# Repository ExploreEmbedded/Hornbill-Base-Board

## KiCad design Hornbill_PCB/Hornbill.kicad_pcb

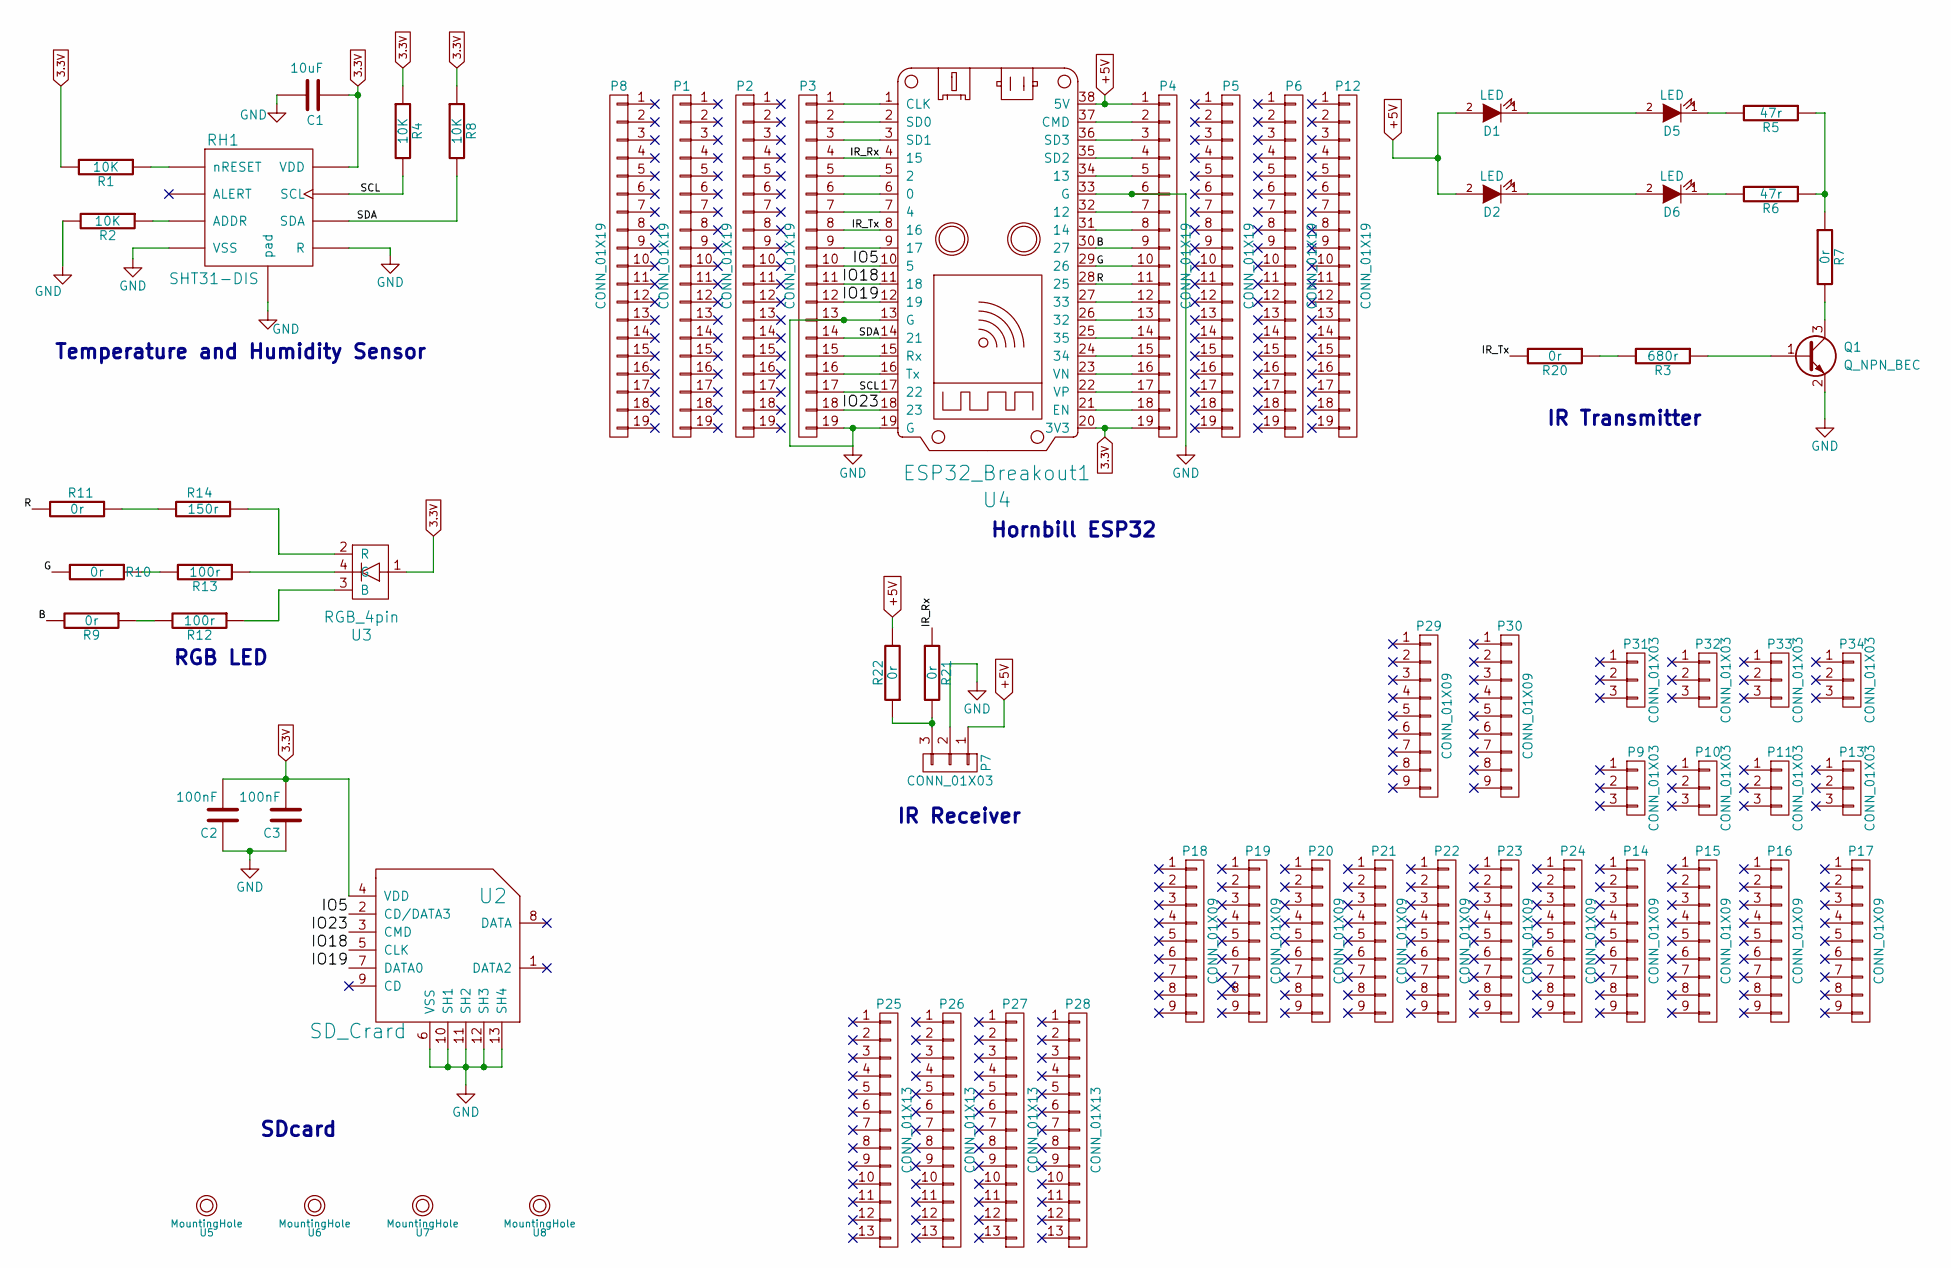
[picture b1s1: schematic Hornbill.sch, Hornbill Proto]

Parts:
C1: 10uF; C_0603_HandSoldering
C2, C3: 100nF; C_0603_HandSoldering
D1, D2, D5, D6: LED; LED-3MM
P1, P2, P3, P4, P5, P6, P8, P12: CONN_01X19; Pin_Header_Straight_1x19_Pitch2.54mm
P7, P9, P10, P11, P13, P31, P32, P33, P34: CONN_01X03; Pin_Header_Straight_1x03_Pitch2.54mm
P14, P15, P16, P17, P18, P19, P20, P21, P22, P23, P24, P29, P30: CONN_01X09; Pin_Header_Straight_1x09_Pitch2.54mm
P25, P26, P27, P28: CONN_01X13; Pin_Header_Straight_1x13_Pitch2.54mm
Q1: Q_NPN_BEC; SOT_23
R1, R2, R4, R8: 10K; R_0603_HandSoldering
R3: 680r; R_0603_HandSoldering
R5, R6: 47r; R_0603_HandSoldering
R7, R9, R10, R11, R20, R21, R22: 0r; R_0603_HandSoldering
R12, R13: 100r; R_0603_HandSoldering
R14: 150r; R_0603_HandSoldering
RH1: SHT31-DIS; DFN-8_SHT-3x-DIS
U2: SD_Crard; Micro_SD
U3: RGB_4pin; RGB_SMD_4pin_New
U4: ESP32_Breakout1; ESP32_Breakout
U5, U6, U7, U8: MountingHole; Mounting

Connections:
3.3V: C1.1, C2.2, C3.2, P4.19, R1.2, R4.1, R8.1, RH1.5 (VDD), U2.4 (VDD), U3.1, U4.20 (3V3)
+5V: D1.2 (A), D2.2 (A), P4.1, P7.1, R22.2, U4.38 (5V)
/B: P4.9, R9.2, U4.30 (27)
/G: P4.10, R10.2, U4.29 (26)
/IO5: P3.10, U2.2 (CD/DATA3), U4.10 (5)
/IO18: P3.11, U2.5 (CLK), U4.11 (18)
/IO19: P3.12, U2.7 (DATA0), U4.12 (19)
/IO23: P3.18, U2.3 (CMD), U4.18 (23)
/IR_Rx: P3.4, R21.1, U4.4 (15)
/IR_Tx: P3.8, R20.2, U4.8 (16)
/R: P4.11, R11.2, U4.28 (25)
/SCL: P3.17, R4.2, RH1.4 (SCL), U4.17 (22)
/SDA: P3.14, R8.2, RH1.1 (SDA), U4.14 (21)
GND: C1.2, C2.1, C3.1, P3.13, P3.19, P4.6, P7.2, Q1.2 (E), R2.2, RH1.7 (R), RH1.8 (VSS), RH1.9 (pad), U2.6 (VSS), U2.10 (SH1), U2.11 (SH2), U2.12 (SH3), U2.13 (SH4), U4.13 (G), U4.19 (G), U4.33 (G)
unnamed: D1.1 (K), D5.2 (A)
unnamed: D2.1 (K), D6.2 (A)
unnamed: D5.1 (K), R5.2
unnamed: D6.1 (K), R6.2
unnamed: P3.1, U4.1 (CLK)
unnamed: P3.2, U4.2 (SD0)
unnamed: P3.3, U4.3 (SD1)
unnamed: P3.5, U4.5 (2)
unnamed: P3.6, U4.6 (0)
unnamed: P3.7, U4.7 (4)
unnamed: P3.9, U4.9 (17)
unnamed: P3.15, U4.15 (Rx)
unnamed: P3.16, U4.16 (Tx)
unnamed: P4.2, U4.37 (CMD)
unnamed: P4.3, U4.36 (SD3)
unnamed: P4.4, U4.35 (SD2)
unnamed: P4.5, U4.34 (13)
unnamed: P4.7, U4.32 (12)
unnamed: P4.8, U4.31 (14)
unnamed: P4.12, U4.27 (33)
unnamed: P4.13, U4.26 (32)
unnamed: P4.14, U4.25 (35)
unnamed: P4.15, U4.24 (34)
unnamed: P4.16, U4.23 (VN)
unnamed: P4.17, U4.22 (VP)
unnamed: P4.18, U4.21 (EN)
unnamed: P7.3, R21.2, R22.1
unnamed: Q1.1 (B), R3.1
unnamed: Q1.3 (C), R7.2
unnamed: R1.1, RH1.6 (nRESET)
unnamed: R2.1, RH1.2 (ADDR)
unnamed: R5.1, R6.1, R7.1
unnamed: R10.1, R13.2
unnamed: R11.1, R14.2
unnamed: R12.1, U3.3 (B)
unnamed: R9.1, R12.2
unnamed: R13.1, U3.4 (G)
unnamed: R14.1, U3.2 (R)
unnamed: R3.2, R20.1

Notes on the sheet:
Temperature and Humidity Sensor
IR Transmitter
SDcard
RGB LED
IR Receiver
Hornbill ESP32

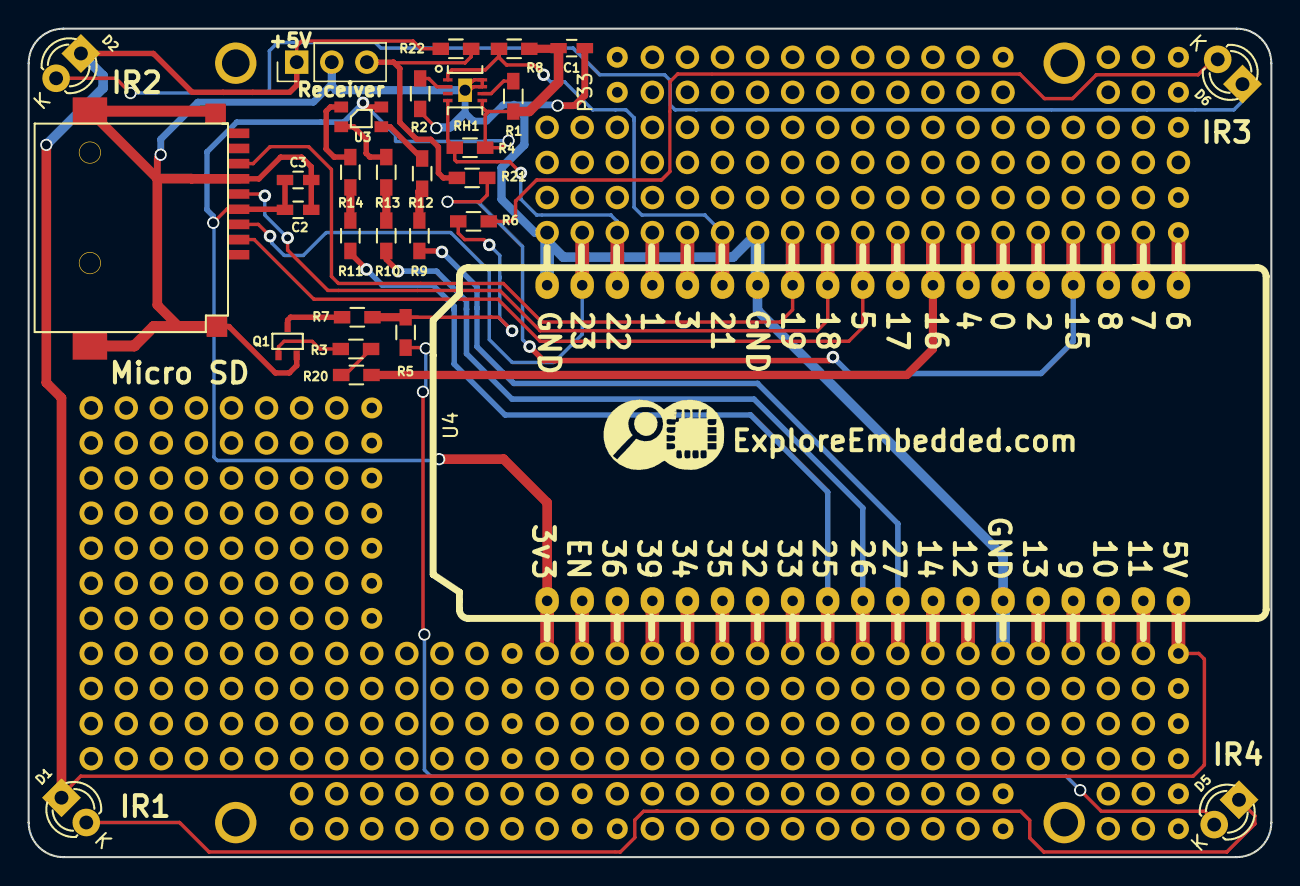
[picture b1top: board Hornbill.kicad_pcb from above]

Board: 2 copper layers, 90.0 x 60.0 mm, 68 parts (0 on the bottom side), 53 nets.

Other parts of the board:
P14#2: CONN_01X01; Logo_8

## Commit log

2016-12-30 Design Files
    Added design files, verify schematic and layout if any changes.. Routing
    not done..
2017-01-03 PCB layout routing completed
2017-03-15 pdf schema
2017-04-24 Chnges done as per issues
2017-04-26 BOM generated
2017-04-27 Logo and Gerber files generted for v0.2
2017-04-27 Hornbill Logo added
2017-05-12 v0.3
2017-05-12 Micro SD socket pin 1 named as NC
2017-05-12 Gerber generated for v0.3
2017-06-12 Process sheet added
